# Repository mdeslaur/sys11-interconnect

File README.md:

# Williams System 11 Interconnect board

This is a replacement interconnect board for use in Williams System 11B
pinball machines. The original part number is D-12313-x (x varies per
game).

Each game has a specific combination of resistor values, jumpers, and
populated connectors. See the manual for each game to know what the
appropriate values are, and which connectors need to be populated.

Swords of Fury and Taxi use a slightly older version of this board that
doesn't have the optocouplers at U2 and U3.

Version 1.0 of this design was tested successfully in Diner.

Change history:  
1.0 - Initial version  
1.1 - Moved some traces further away from J19  

To Do:  
- Clean up the schematic, goal was to make a PCB, not a schematic.  
- Modify Molex connector footprints to make pads longer  

Marc Deslauriers
2022-05-17

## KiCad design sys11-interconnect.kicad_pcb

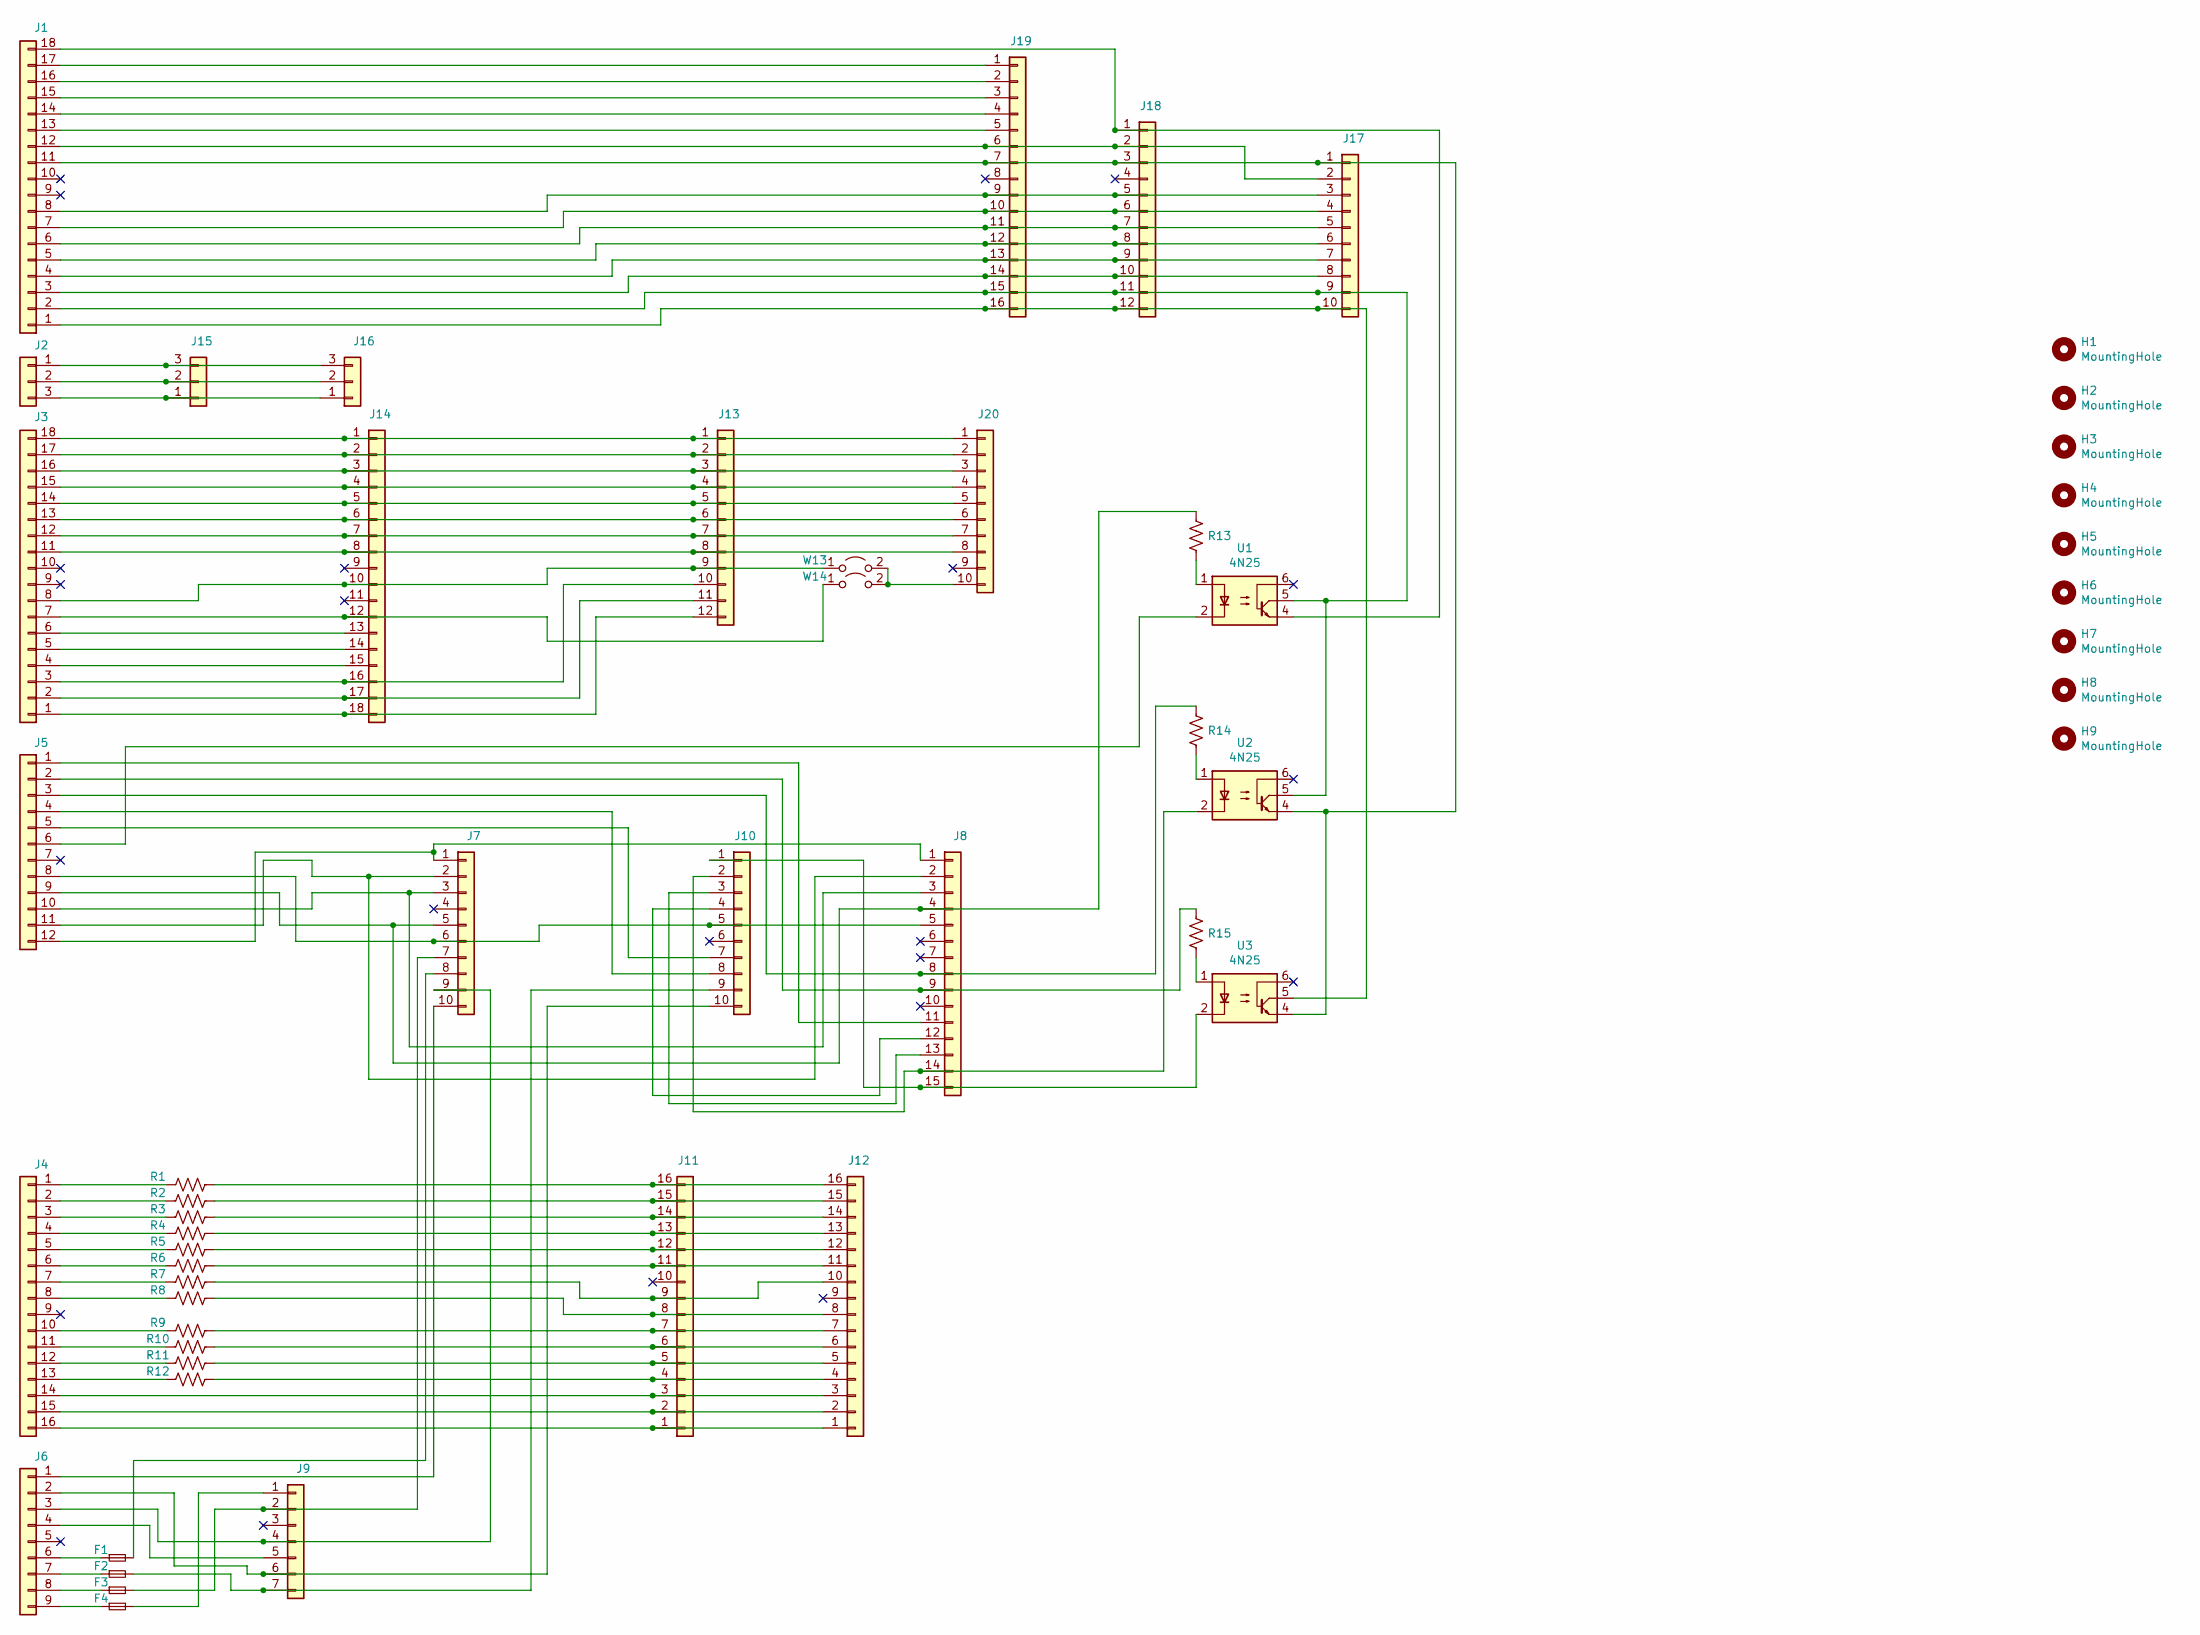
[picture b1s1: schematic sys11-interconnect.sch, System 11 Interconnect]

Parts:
F1, F2, F3, F4: Fuse_Small; Littelfuse_Inc-03540101ZXGY-MFG-combo
H1, H2, H3, H4, H5, H6, H7, H8, H9: MountingHole; MountingHole_4.5mm
J1, J3, J14: Conn_01x18; Molex_KK-396_A-41791-0018_1x18_P3.96mm_Vertical
J2, J15, J16: Conn_01x03; Molex_KK-396_A-41791-0003_1x03_P3.96mm_Vertical
J4, J11, J12, J19: Conn_01x16; Molex_KK-396_A-41791-0016_1x16_P3.96mm_Vertical
J5, J13, J18: Conn_01x12; Molex_KK-396_A-41791-0012_1x12_P3.96mm_Vertical
J6: Conn_01x09; Molex_KK-396_A-41791-0009_1x09_P3.96mm_Vertical
J7, J10, J17, J20: Conn_01x10; Molex_KK-396_A-41791-0010_1x10_P3.96mm_Vertical
J8: Conn_01x15; Molex_KK-396_A-41791-0015_1x15_P3.96mm_Vertical
J9: Conn_01x07; Molex_KK-396_A-41791-0007_1x07_P3.96mm_Vertical
R1, R2, R3, R4, R5, R6, R7, R8, R9, R10, R11, R12: R_US; R_Axial_DIN0922_L20.0mm_D9.0mm_P30.48mm_Horizontal-combo
R13, R14, R15: R_US; R_Axial_DIN0922_L20.0mm_D9.0mm_P30.48mm_Horizontal
U1, U2, U3: 4N25; DIP-6_W7.62mm
W13, W14: Jumper_2_Open; R_Axial_DIN0309_L9.0mm_D3.2mm_P12.70mm_Horizontal

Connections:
unnamed: F1.1, J6.6
unnamed: F1.2, J7.8
unnamed: F2.1, J6.7
unnamed: F2.2, J9.7, J10.9
unnamed: F3.1, J6.8
unnamed: F3.2, J7.7, J9.2
unnamed: F4.1, J6.9
unnamed: F4.2, J9.1
unnamed: J1.1, J17.10, J18.12, J19.16, U3.5
unnamed: J1.2, J17.9, J18.11, J19.15, U1.5, U2.5
unnamed: J1.3, J17.8, J18.10, J19.14
unnamed: J1.4, J17.7, J18.9, J19.13
unnamed: J1.5, J17.6, J18.8, J19.12
unnamed: J1.6, J17.5, J18.7, J19.11
unnamed: J1.7, J17.4, J18.6, J19.10
unnamed: J1.8, J17.3, J18.5, J19.9
unnamed: J1.11, J17.1, J18.3, J19.7, U2.4, U3.4
unnamed: J1.12, J17.2, J18.2, J19.6
unnamed: J1.13, J19.5
unnamed: J1.14, J19.4
unnamed: J1.15, J19.3
unnamed: J1.16, J19.2
unnamed: J1.17, J19.1
unnamed: J1.18, J18.1, U1.4
unnamed: J4.1, R1.2
unnamed: J4.2, R2.2
unnamed: J4.3, R3.2
unnamed: J4.4, R4.2
unnamed: J4.5, R5.2
unnamed: J4.6, R6.2
unnamed: J4.7, R7.2
unnamed: J4.8, R8.2
unnamed: J4.10, R9.2
unnamed: J4.11, R10.2
unnamed: J4.12, R11.2
unnamed: J4.13, R12.2
unnamed: J5.1, J8.11
unnamed: J5.2, J8.9, R15.1
unnamed: J5.3, J8.8, R14.1
unnamed: J5.6, U1.2
unnamed: J5.9, J7.5, J8.4, R13.1
unnamed: J5.10, J7.3, J8.3
unnamed: J5.11, J7.2, J8.2
unnamed: J5.12, J7.1, J8.1
unnamed: J6.1, J7.10
unnamed: J6.3, J7.9, J9.4
unnamed: J6.4, J9.5
unnamed: J8.15, J10.1, U3.2
unnamed: J8.14, J10.2, U2.2
unnamed: J8.13, J10.3
unnamed: J8.12, J10.4
unnamed: J5.8, J7.6, J8.5, J10.5
unnamed: J5.5, J10.7
unnamed: J5.4, J10.8
unnamed: J6.2, J9.6, J10.10
unnamed: J4.16, J11.1, J12.1
unnamed: J4.15, J11.2, J12.2
unnamed: J4.14, J11.3, J12.3
unnamed: J11.4, J12.4, R12.1
unnamed: J11.5, J12.5, R11.1
unnamed: J11.6, J12.6, R10.1
unnamed: J11.7, J12.7, R9.1
unnamed: J11.8, J12.8, R8.1
unnamed: J11.9, J12.10, R7.1
unnamed: J11.11, J12.11, R6.1
unnamed: J11.12, J12.12, R5.1
unnamed: J11.13, J12.13, R4.1
unnamed: J11.14, J12.14, R3.1
unnamed: J11.15, J12.15, R2.1
unnamed: J11.16, J12.16, R1.1
unnamed: J3.18, J13.1, J14.1, J20.1
unnamed: J3.17, J13.2, J14.2, J20.2
unnamed: J3.16, J13.3, J14.3, J20.3
unnamed: J3.15, J13.4, J14.4, J20.4
unnamed: J3.14, J13.5, J14.5, J20.5
unnamed: J3.13, J13.6, J14.6, J20.6
unnamed: J3.12, J13.7, J14.7, J20.7
unnamed: J3.11, J13.8, J14.8, J20.8
unnamed: J3.8, J13.9, J14.10, W13.1 (A)
unnamed: J3.3, J13.10, J14.16
unnamed: J3.2, J13.11, J14.17
unnamed: J3.1, J13.12, J14.18
unnamed: J3.7, J14.12, W14.1 (A)
unnamed: J3.6, J14.13
unnamed: J3.5, J14.14
unnamed: J3.4, J14.15
unnamed: J2.3, J15.1, J16.1
unnamed: J2.2, J15.2, J16.2
unnamed: J2.1, J15.3, J16.3
unnamed: J20.10, W13.2 (B), W14.2 (B)
unnamed: R13.2, U1.1
unnamed: R14.2, U2.1
unnamed: R15.2, U3.1

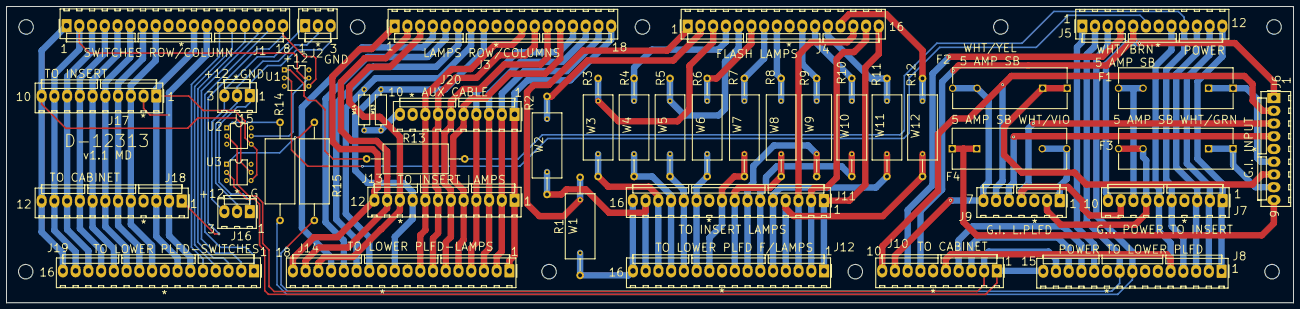
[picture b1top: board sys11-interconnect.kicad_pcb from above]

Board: 2 copper layers, 400.1 x 92.1 mm, 53 parts (0 on the bottom side), 93 nets.

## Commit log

2022-03-18 added notes to README.md
